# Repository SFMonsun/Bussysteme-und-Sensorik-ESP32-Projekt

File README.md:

"# Bussysteme-und-Sensorik-ESP32-Projekt"

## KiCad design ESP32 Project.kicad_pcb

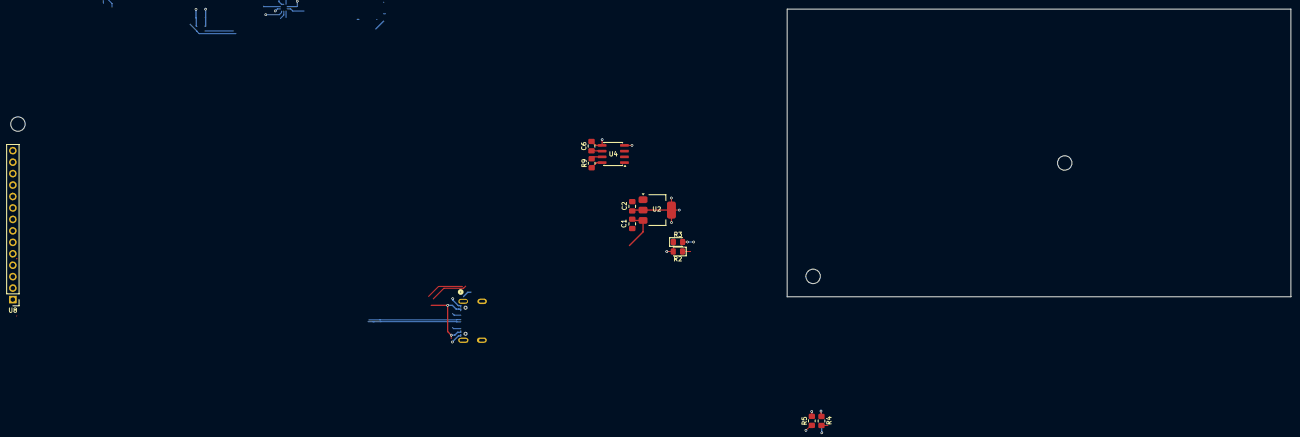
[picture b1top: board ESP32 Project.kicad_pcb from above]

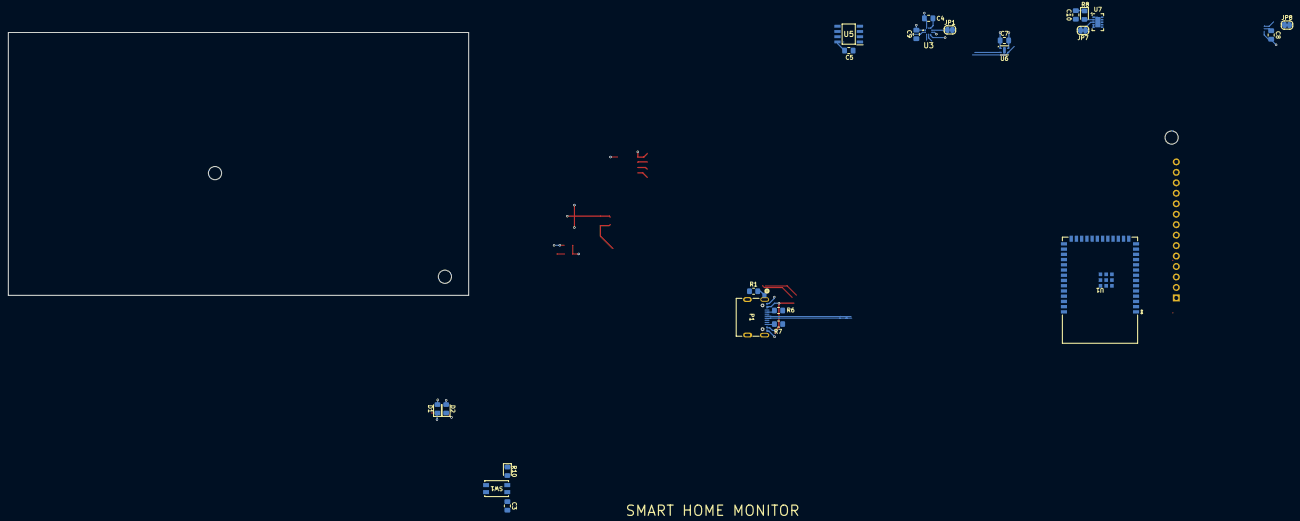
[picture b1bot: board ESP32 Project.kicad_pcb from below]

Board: 4 copper layers, 35 parts (24 on the bottom side), 27 nets.

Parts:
C1, C2: 10uF; C_0805_2012Metric_Pad1.18x1.45mm_HandSolder
C3, C4, C5, C6, C7, C8, C9, C10: 100nF; C_0805_2012Metric_Pad1.18x1.45mm_HandSolder
D1, D2: LED; LED_0805_2012Metric_Pad1.15x1.40mm_HandSolder
JP1, JP7, JP8: SolderJumper_2_Open; SolderJumper-2_P1.3mm_Open_RoundedPad1.0x1.5mm
P1: USB_C_Plug_USB2.0; USB4105-GF-A-120
R1, R4, R5: 1M; R_0805_2012Metric_Pad1.20x1.40mm_HandSolder
R2, R3, R10: 10k; LED_0805_2012Metric_Pad1.15x1.40mm_HandSolder
R6, R7: 5.1k; R_0805_2012Metric_Pad1.20x1.40mm_HandSolder
R8: 4.7k; LED_0805_2012Metric_Pad1.15x1.40mm_HandSolder
R9: R_Small; R_0805_2012Metric_Pad1.20x1.40mm_HandSolder
SW1: EVQ-P2K02Q; EVQP2K_PAN BTN
U1: ESP32-S3-WROOM-1-N8R2; ESP32-S3-WROOM-1_EXP
U2: AMS1117; SOT-223-3_TabPin2
U3: BMP390
U4: INA219AxD; SOIC-8_3.9x4.9mm_P1.27mm
U5: LM75B; LM75BD,118
U6: SHTC3; Sensirion_DFN-4-1EP_2x2mm_P1mm_EP0.7x1.6mm
U7: CCS811; AMS_LGA-10-1EP_2.7x4mm_P0.6mm
U8: PinHeader_1x14_P2.54mm_Vertical

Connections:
+3.3V: C2.1, C4.1, C5.1, C6.2, C7.2, C8.2, C9.1, C10.2, R2.2, R3.1, R5.1, R8.1, R10.1, U1.2 (3V3), U2.2 (VO), U3.1 (VDDIO), U3.6 (CSB), U3.10 (VDD), U4.5 (VS), U5.8 (+Vs), U6.1 (VDD), U7.6 (VDD), U8.1 (VCC), U8.8 (LED)
+5V_in: P1.A4 (VBUS), P1.A9 (VBUS), P1.B4 (VBUS), P1.B9 (VBUS), R4.1, R9.1, U4.8 (IN+)
+5V_out: C1.1, R9.2, U2.3 (VI), U4.7 (IN-)
D+: P1.A6 (D+), U1.14 (IO20)
D-: P1.A7 (D-), U1.13 (IO19)
EN: C3.1, R10.2, SW1.1, SW1.2, U1.3 (EN)
GND: C1.2, C2.2, C3.2, C4.2, C5.2, C6.1, C7.1, C8.1, C9.2, C10.1, D1.1 (K), D2.1 (K), P1.A1 (GND), P1.A12 (GND), P1.B1 (GND), P1.B12 (GND), R1.2, R6.2, R7.2, SW1.3, SW1.4, U1.1 (GND), U1.40 (GND), U1.41 (GND), U1.42 (GND), U1.43 (GND), U1.44 (GND), U1.45 (GND), U1.46 (GND), U1.47 (GND), U1.48 (GND), U1.49 (GND), U2.1 (ADJ), U3.3 (VSS), U3.5 (SDO), U3.8 (VSS), U3.9 (VSS), U4.1 (A1), U4.2 (A0), U4.6 (GND), U5.4 (GND), U5.5 (A2), U5.6 (A1), U5.7 (A0), U6.4 (VSS), U7.1 (ADDR), U7.7 (~WAKE), U7.11 (GND), U8.2 (GND)
unnamed: D1.2 (A), R4.2
unnamed: D2.2 (A), R5.2
unnamed: JP1.1 (A), U3.7 (INT)
unnamed: JP7.1 (A), U7.3 (~INT)
unnamed: JP8.1 (A), U7.8 (AUX)
unnamed: P1.A5 (CC), R6.1
unnamed: P1.S1 (SHIELD), R1.1
unnamed: P1.B5 (VCONN), R7.1
unnamed: U1.4 (IO4), U8.3 (CS)
unnamed: U1.5 (IO5), U8.4 (RESET)
unnamed: U1.6 (IO6), U8.5 (DC/RS)
unnamed: U1.7 (IO7), U8.6 (SDI(MOSI)), U8.12 (T_DIN)
unnamed: U1.8 (IO15), U8.7 (SCK), U8.10 (T_CLK)
unnamed: U1.9 (IO16), U8.9 (SDO(MISO)), U8.13 (T_DO)
unnamed: U1.10 (IO17), U8.11 (T_CS)
unnamed: U1.11 (IO18), U8.14 (T_IRQ)
unnamed: U7.4 (PWM), U7.5 (Sense)
unnamed: R8.2, U7.2 (~RESET)
SCL: R2.1, U1.17 (IO9), U3.4 (SDI), U4.3 (SDA), U5.2 (SCL), U6.3 (SDA), U7.10 (SCL)
SDA: R3.2, U1.12 (IO8), U3.2 (SCK), U4.4 (SCL), U5.1 (SDA), U6.2 (SCL), U7.9 (SDA)

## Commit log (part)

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2025-10-06 Initial Project setup
2025-10-06 just parts
2025-10-06 parts
2025-10-07 this
2025-10-17 added alot, pcb first prototype 4 layers
2025-11-11 newstuff
